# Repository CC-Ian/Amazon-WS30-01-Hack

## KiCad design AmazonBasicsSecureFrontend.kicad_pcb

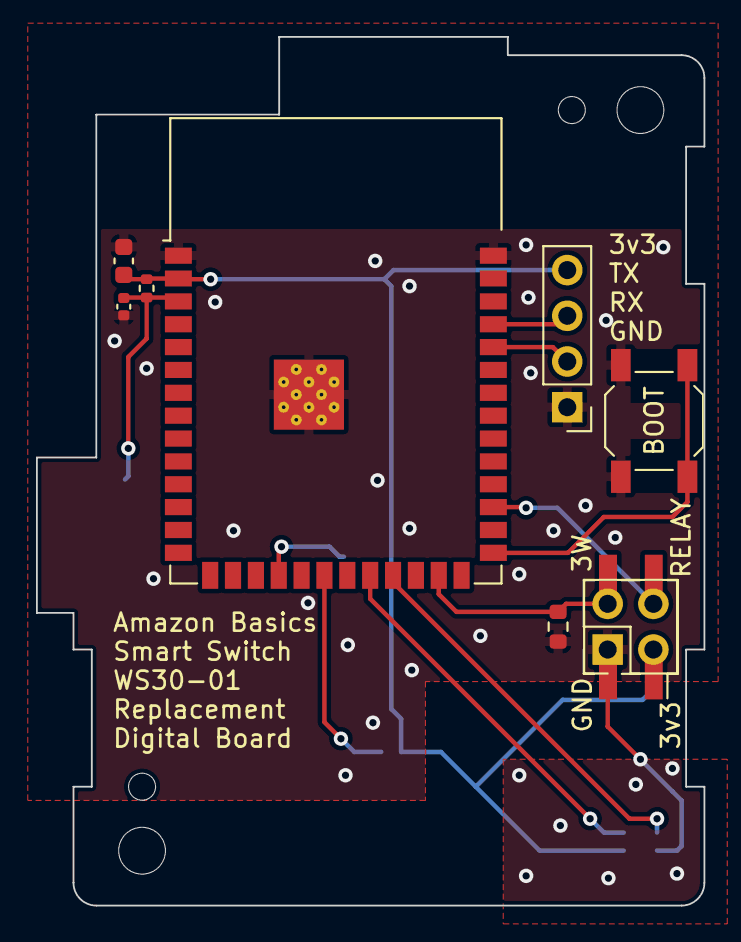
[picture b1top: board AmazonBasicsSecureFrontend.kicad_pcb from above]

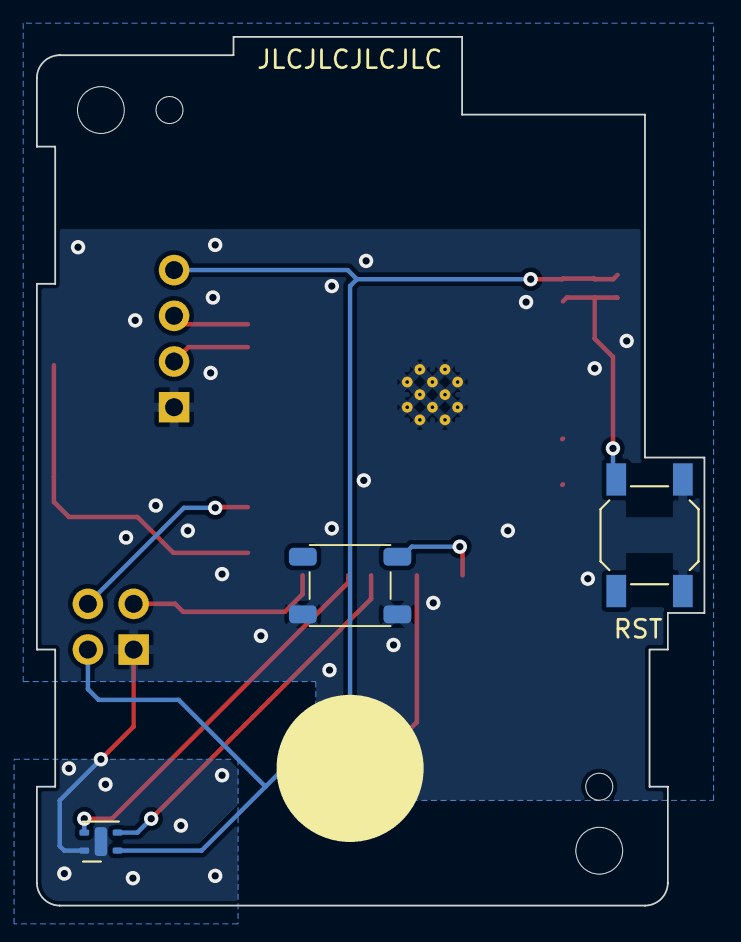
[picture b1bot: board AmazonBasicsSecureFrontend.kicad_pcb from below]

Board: 2 copper layers, 37.1 x 48.3 mm, 10 parts (3 on the bottom side), 11 nets.

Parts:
C1: 100n; C_0402_1005Metric
J1: Conn_01x04_Socket; PinHeader_1x04_P2.54mm_Vertical
J2: Conn_02x02_Counter_Clockwise; PinSocket_2x02_P2.54mm_Vertical
R1: 10k; R_0402_1005Metric
R2: R_Small; R_0603_1608Metric
SW1, SW2: SW_Push; SW_SPST_SKQG_WithStem
U1: ESP32-S2-SOLO-2; ESP32-S3-WROOM-1
U2: SHTC3; Sensirion_DFN-4-1EP_2x2mm_P1mm_EP0.7x1.6mm
U3: LED_WS2812B-2020_PLCC4_2.0x2.0mm

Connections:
3W: J2.3, R2.1, U1.25 (IO34)
+3V3: J1.4, J2.2, R1.2, U1.2 (VCC), U2.1 (VDD), U3.4 (VCC)
BOOT: SW2.2, U1.27 (IO0)
GND: C1.2, J1.1, J2.1, R2.2, SW1.2, SW2.1, U1.1 (GND), U1.40 (GND), U1.41 (EPAD), U2.4 (VSS), U2.5 (NC), U3.2 (GND)
LED_IN: U1.20 (IO12), U3.3 (DIN)
RELAY: J2.4, U1.29 (IO36)
RST: C1.1, R1.1, SW1.1, U1.3 (EN)
RX: J1.2, U1.36 (RX)
SCL: U1.22 (IO14), U2.2 (SCL)
SDA: U1.23 (IO21), U2.3 (SDA)
TX: J1.3, U1.37 (TX)

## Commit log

2023-10-29 Restructure and clean up
